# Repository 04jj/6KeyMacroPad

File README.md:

# 6KeyMacroPad

Feel free to use/modify the files to make your own macropad! ai03's keyboard design wiki is very helpful, I highly recommend reading it.
I am including all PCB files and CAD files for the case. 

Some pics (I 3D printed and sanded the keycaps by hand so they are not the most even/nice):

# Specs
* In-key RGB lighting 
* Hot-swappable
* Atmega32U2 MCU
* USB-C Port
* Acrylic stack case
* QMK/VIA compatible

# Firmware/QMK/VIA support
Use zadig to install the WinUSB drivers onto the Atmega32u2
Use qmk msys to compile the .hex file to flash onto the MCU
Use qmk toolbox to flash the MCU (to turn the MCU into bootloader mode, press the reset switch on the back of the PCB)
  - There are default and via keymaps (I recommend using the via one so you can easily map macros/your own keys/adjust lighting easily)

# PCB/Build Files
See folder named PCB Gerber files to get the required files to order the PCB. I did not order PCBA but you can do so if you don't want to hand-solder by referencing the BOM and PCB/Schematic files.

For the case, I provided the .step files in the folder named Case Step Files for each layer of the acrylic stack. I used M2 Screws with some washers and spacers to secure everything together (w/o washers M3 screws and spacers should work fine - might require a little bit of sanding).

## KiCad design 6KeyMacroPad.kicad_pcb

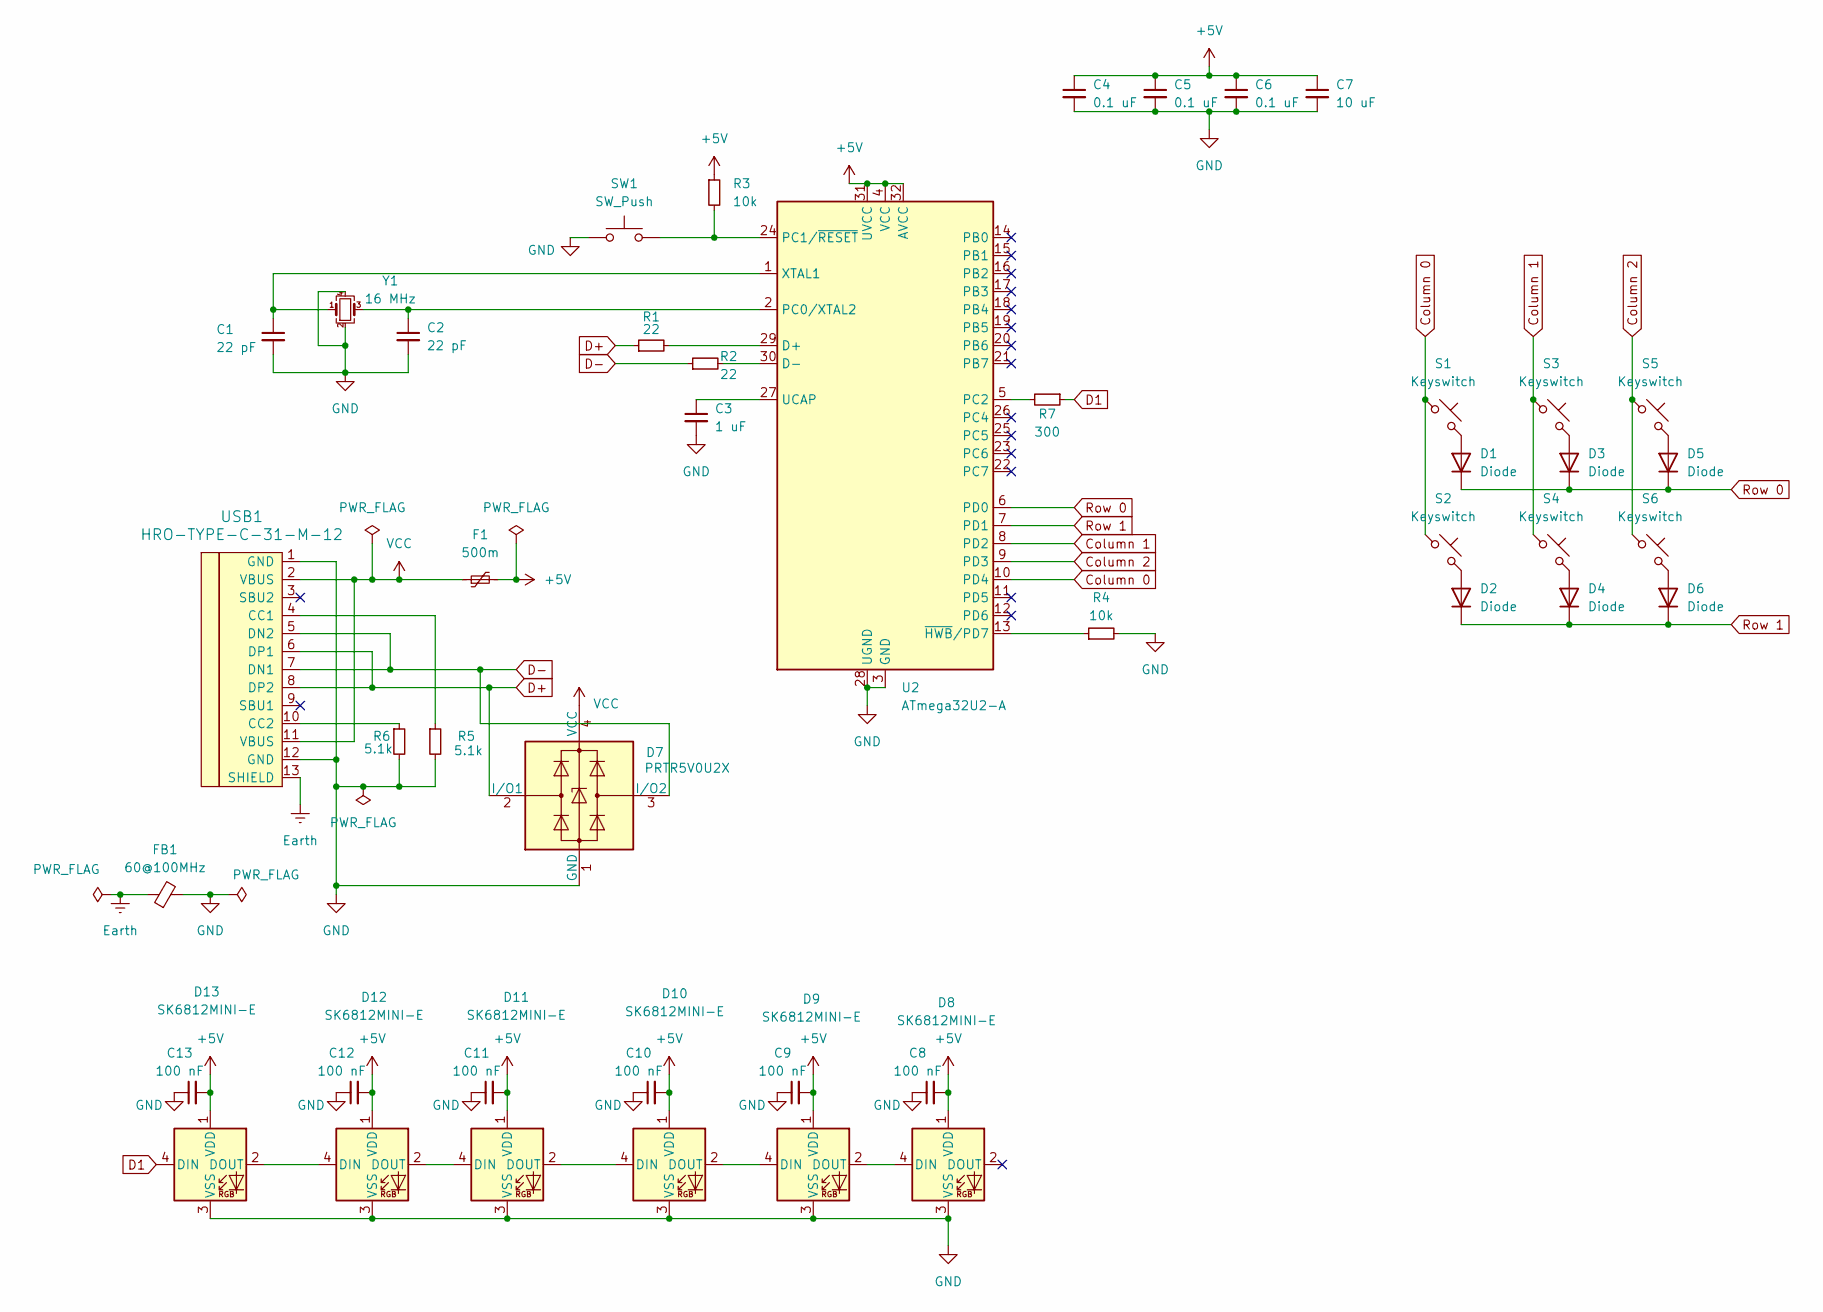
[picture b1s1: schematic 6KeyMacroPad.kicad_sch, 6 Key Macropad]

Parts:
C1, C2: 22 pF; C_0805_2012Metric
C3: 1 uF; C_0805_2012Metric
C4, C5, C6: 0.1 uF; C_0805_2012Metric
C7: 10 uF; C_0805_2012Metric
C8, C9, C10, C11, C12, C13: 100 nF; C_0805_2012Metric
D1, D2, D3, D4, D5, D6: Diode; D_SOD-123
D7: PRTR5V0U2X; SOT-143
D8, D9, D10, D11, D12, D13: SK6812MINI-E; MX_SK6812MINI-E
F1: 500m; Fuse_1206_3216Metric
FB1: 60@100MHz; L_0805_2012Metric_Pad1.15x1.40mm_HandSolder
R1, R2: 22; R_0805_2012Metric
R3, R4: 10k; R_0805_2012Metric
R5, R6: 5.1k; R_0805_2012Metric
R7: 300; R_0805_2012Metric
S1, S2, S3, S4, S5, S6: Keyswitch; Hotswap_MX_1.00u
SW1: SW_Push; SW_SPST_SKQG_WithStem
U2: ATmega32U2-A; TQFP-32_7x7mm_P0.8mm
USB1: HRO-TYPE-C-31-M-12; HRO-TYPE-C-31-M-12-HandSoldering
Y1: 16 MHz; Crystal_SMD_3225-4Pin_3.2x2.5mm_HandSoldering

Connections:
+5V: C4.1, C5.1, C6.1, C7.1, C8.2, C9.2, C10.2, C11.2, C12.2, C13.2, D8.1 (VDD), D9.1 (VDD), D10.1 (VDD), D11.1 (VDD), D12.1 (VDD), D13.1 (VDD), F1.2, R3.1, U2.4 (VCC), U2.31 (UVCC), U2.32 (AVCC)
Column 0: S1.1, S2.1, U2.10 (PD4)
Column 1: S3.1, S4.1, U2.8 (PD2)
Column 2: S5.1, S6.1, U2.9 (PD3)
D1: D13.4 (DIN), R7.1
D+: D7.2 (I/O1), R1.1, USB1.6 (DP1), USB1.8 (DP2)
D-: D7.3 (I/O2), R2.1, USB1.5 (DN2), USB1.7 (DN1)
Earth: FB1.1, USB1.13 (SHIELD)
GND: C1.2, C2.2, C3.2, C4.2, C5.2, C6.2, C7.2, C8.1, C9.1, C10.1, C11.1, C12.1, C13.1, D7.1 (GND), D8.3 (VSS), D9.3 (VSS), D10.3 (VSS), D11.3 (VSS), D12.3 (VSS), D13.3 (VSS), FB1.2, R4.2, R5.2, R6.2, SW1.1, U2.3 (GND), U2.28 (UGND), USB1.1 (GND), USB1.12 (GND), Y1.2, Y1.4
unnamed: D1.2 (A), S1.2
unnamed: D2.2 (A), S2.2
unnamed: D3.2 (A), S3.2
unnamed: D4.2 (A), S4.2
unnamed: D5.2 (A), S5.2
unnamed: D6.2 (A), S6.2
unnamed: D8.4 (DIN), D9.2 (DOUT)
unnamed: D10.4 (DIN), D11.2 (DOUT)
unnamed: D9.4 (DIN), D10.2 (DOUT)
unnamed: D11.4 (DIN), D12.2 (DOUT)
unnamed: D12.4 (DIN), D13.2 (DOUT)
unnamed: R1.2, U2.29 (D+)
unnamed: R2.2, U2.30 (D-)
unnamed: C2.1, U2.2 (PC0/XTAL2), Y1.3
unnamed: R3.2, SW1.2, U2.24 (PC1/~RESET)
unnamed: R7.2, U2.5 (PC2)
unnamed: C3.1, U2.27 (UCAP)
unnamed: C1.1, U2.1 (XTAL1), Y1.1
unnamed: R4.1, U2.13 (~HWB/PD7)
unnamed: R5.1, USB1.4 (CC1)
unnamed: R6.1, USB1.10 (CC2)
Row 0: D1.1 (K), D3.1 (K), D5.1 (K), U2.6 (PD0)
Row 1: D2.1 (K), D4.1 (K), D6.1 (K), U2.7 (PD1)
VCC: D7.4 (VCC), F1.1, USB1.2 (VBUS), USB1.11 (VBUS)

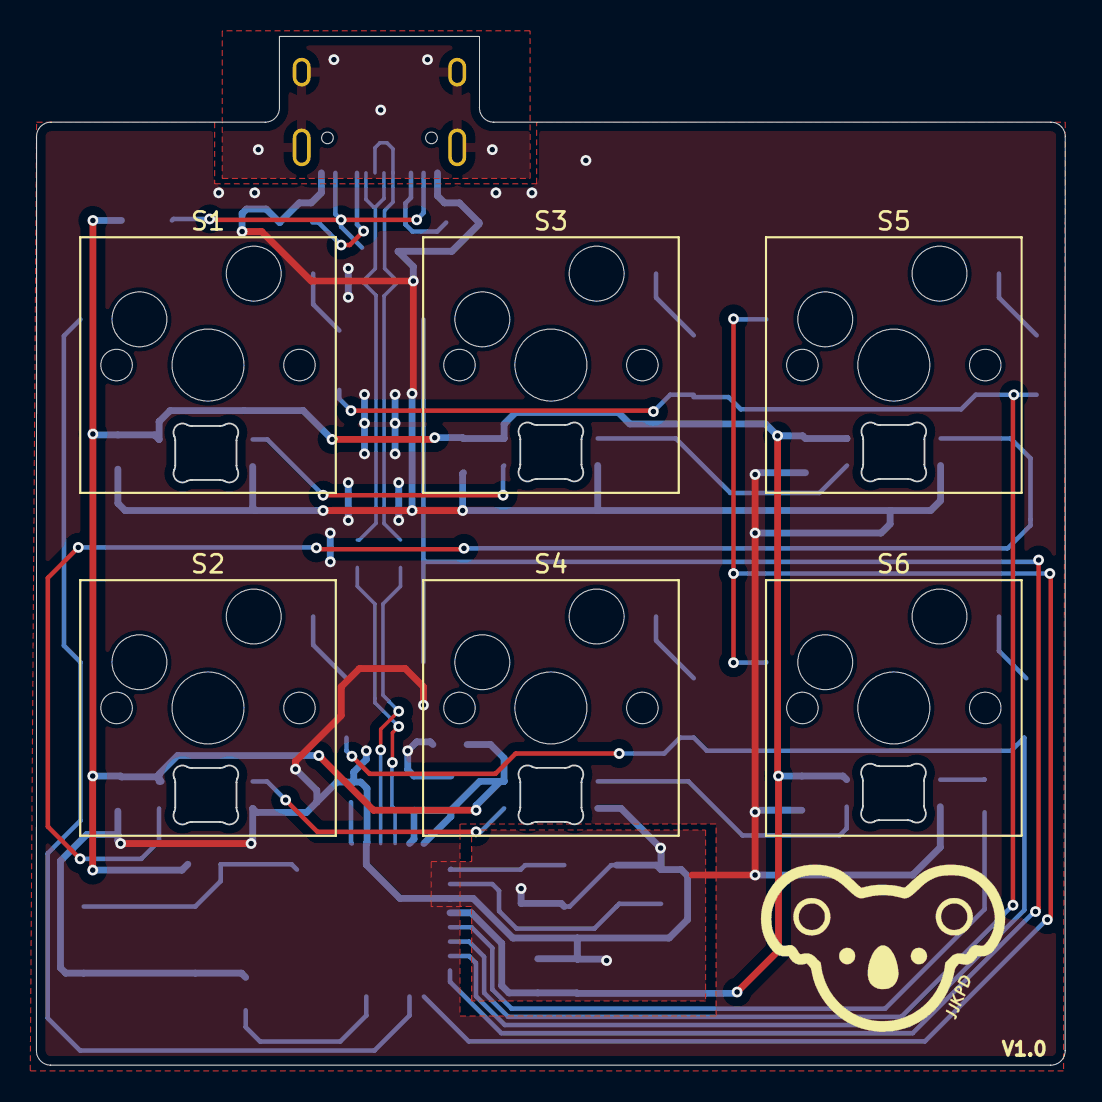
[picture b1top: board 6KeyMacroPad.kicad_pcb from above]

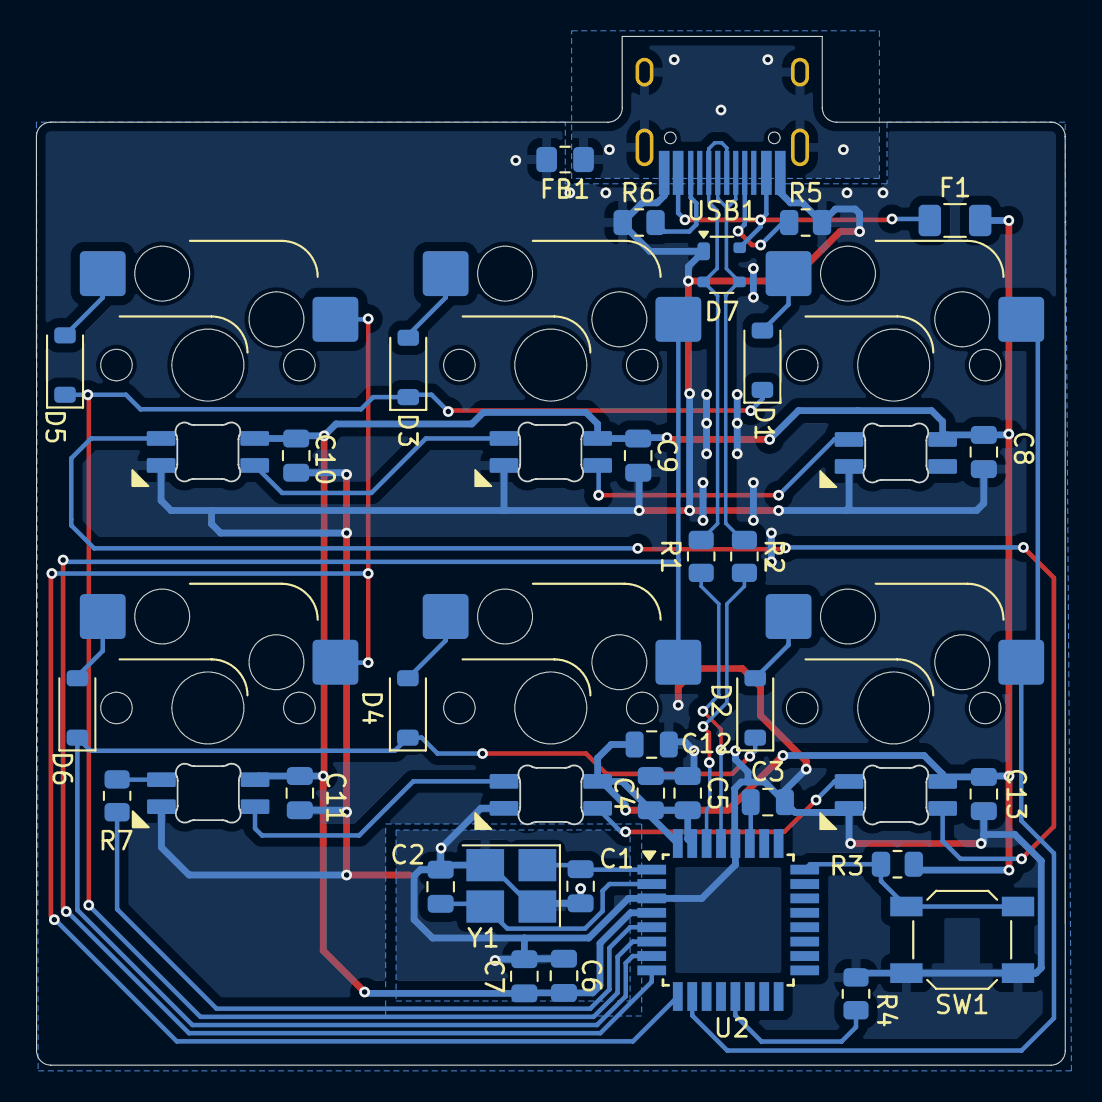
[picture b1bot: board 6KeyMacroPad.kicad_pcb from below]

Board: 2 copper layers, 57.1 x 57.1 mm, 46 parts (33 on the bottom side), 33 nets.

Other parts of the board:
Ref**: Val**; jjkpdlogo

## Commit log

2024-05-27 schematic updates
    - added WS2812B leds
    - added ESD: PRTR5V0U2X, USB 2.0 Type-C connector: HRO-TYPE-C-31-M12
    - ERC checked
2024-05-31 assign footprints
2024-06-01 board layout updates
2024-06-23 footprint edits, routing updates
    drc checked
2024-06-24 manufacturing files changed
2024-07-14 add qmk/via support
2024-07-21 Add step files, firmware updates, organizing files
